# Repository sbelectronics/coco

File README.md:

# CoCo Projects

Assorted hardware and software projects for the TRS-80 Color Computer,
by Dr. Scott M. Baker — <https://www.smbaker.com/>

## [coco-bubble](coco-bubble/)

A cartridge that puts 128 KB of Intel 7110 **magnetic bubble memory**
behind a Disk BASIC-compatible command set: `DIR`, `SAVE`, `LOAD`,
`OPEN`, `COPY`, direct-access files and the rest work as they do on a
disk system, over a non-volatile solid-state medium with no moving
parts. The 16 KB ROM writes files byte-for-byte as Disk BASIC would, so
they move to and from real floppies with `COPY`, and a floppy controller
alongside it in a Multi-Pak becomes drives 1 to 3. Includes the ROM
source, the PLD for the bus interface, a parts list and assembly notes,
an emulator test suite, and a detailed account of both the hardware and
the ROM in [HOW-IT-WORKS.md](coco-bubble/HOW-IT-WORKS.md).

## [radio](radio/)

An **AM/FM radio cartridge**. Plug it in and the CoCo boots into a radio
player: big frequency digits, seek, stereo and signal indicators, twelve
named presets that live in the cartridge's own EEPROM, and audio through
the computer's TV or monitor sound. The receiver is an NXP TEF6686
car-radio tuner module; the 6809 drives it over I2C bit-banged through a
latch, and apart from the module the cartridge is just an EEPROM, a 22V10
PLD, a latch, a buffer and a dual op-amp. Works on a CoCo 1, 2 or 3,
directly or in a Multi-Pak. Includes the ROM source, the PLD, the build
tooling (the tuner's NXP firmware patch is fetched at build time, not
distributed), and [HOW-IT-WORKS.md](radio/HOW-IT-WORKS.md) on the
address decode, the tuner bring-up, how the ROM rewrites its own EEPROM,
and why seek is a host loop.

## [multicart-videocart](multicart-videocart/)

Two Raspberry Pi Pico 2 W cartridges for the CoCo 1/2 that hold your
whole ROM collection — pick a game from the OLED menu or a web browser
and the CoCo reboots straight into it. The **multicart** is the ROM
cartridge; the **videocart** is the same cartridge plus HDMI video and
audio out, rendering the VDG display by snooping the cartridge bus.
Includes firmware, schematics, gerbers, and an architectural guide in
[HOW-IT-WORKS.md](multicart-videocart/HOW-IT-WORKS.md).

## [realtalker](realtalker/)

My clone of the Colorware RealTalker speech synthesizer cartridge,
which used the Votrax SC-01-A speech IC. Includes the recreated
schematic and board files, notes on the original version 1 (CoCo 1) and
version 2 (CoCo 2) hardware, and BASIC and Python examples for driving
it.

## [cocoxt](cocoxt/)

A clone of the Burke & Burke CoCo XT hard disk interface, which puts a
PC/XT-class MFM controller (WD1002-WX1 and friends) on the CoCo's
cartridge bus, along with a long write-up on using it from **Disk
Extended Color BASIC** with B&B's Hyper-I/O rather than OS-9: setup
sequence, driver gotchas, MSA sizing, booting Hyper-I/O from ROM, and
why the address lines are inverted. Includes schematics and gerbers for
two board revisions (one adds an onboard 27C128 socket; untested) and
tools for verifying a drive image from a Gesswein MFM emulator.

## [MPI/TheLittleEngineers](MPI/TheLittleEngineers/)

A 3D-printable case (STL files) I made for the Multi-Pak Interface by
TheLittleEngineers
([CoCoDragon-MultiPakInterface](https://github.com/TheLittleEngineers/CoCoDragon-MultiPakInterface-CC-Multi-Pak_Version_1.2)).
Assembly requires M2.5 threadserts and machine screws.

## [disks](disks/)

Tools for building my disk images: a Makefile, some BASIC demo programs,
and `ccctobin.py` for converting CCC files into BIN files for the
CocoSDC.

## Related projects

- [coco-hdmi](https://github.com/sbelectronics/coco-hdmi) — an
  FPGA-based interposer (Tang Nano 9K) that adds native digital HDMI
  output to the CoCo 2 by intercepting the VDG's signals, rendering
  video at 720×480p with 48 kHz audio.

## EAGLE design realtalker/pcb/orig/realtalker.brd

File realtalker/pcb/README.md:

Colorware Realtalker Schematics
http://www.smbaker.com/

NOTE! CAUTION! These schematics are unverified.

These directories contain reverse-engineered schematics for the
colorware realtalker for the trs-80 color computer. Note that the
version 1 of the realtalker was for coco-1 only as it relied on
the +12V from the cartridge port. A version-2 was added for the coco-2
which at a minimum included an external power supply. I also found
that the version-1 when used on a Coco-2 produces audio that is
clipped and distorted. Adding a potentiometer between the realtalker's
output and the coco's cartridge sound input resolved this issue for
me. Unknown what other changes the version-2 may have included.

Also present is a schematic for a revised version that I am working
on that will include a few minor improvements.

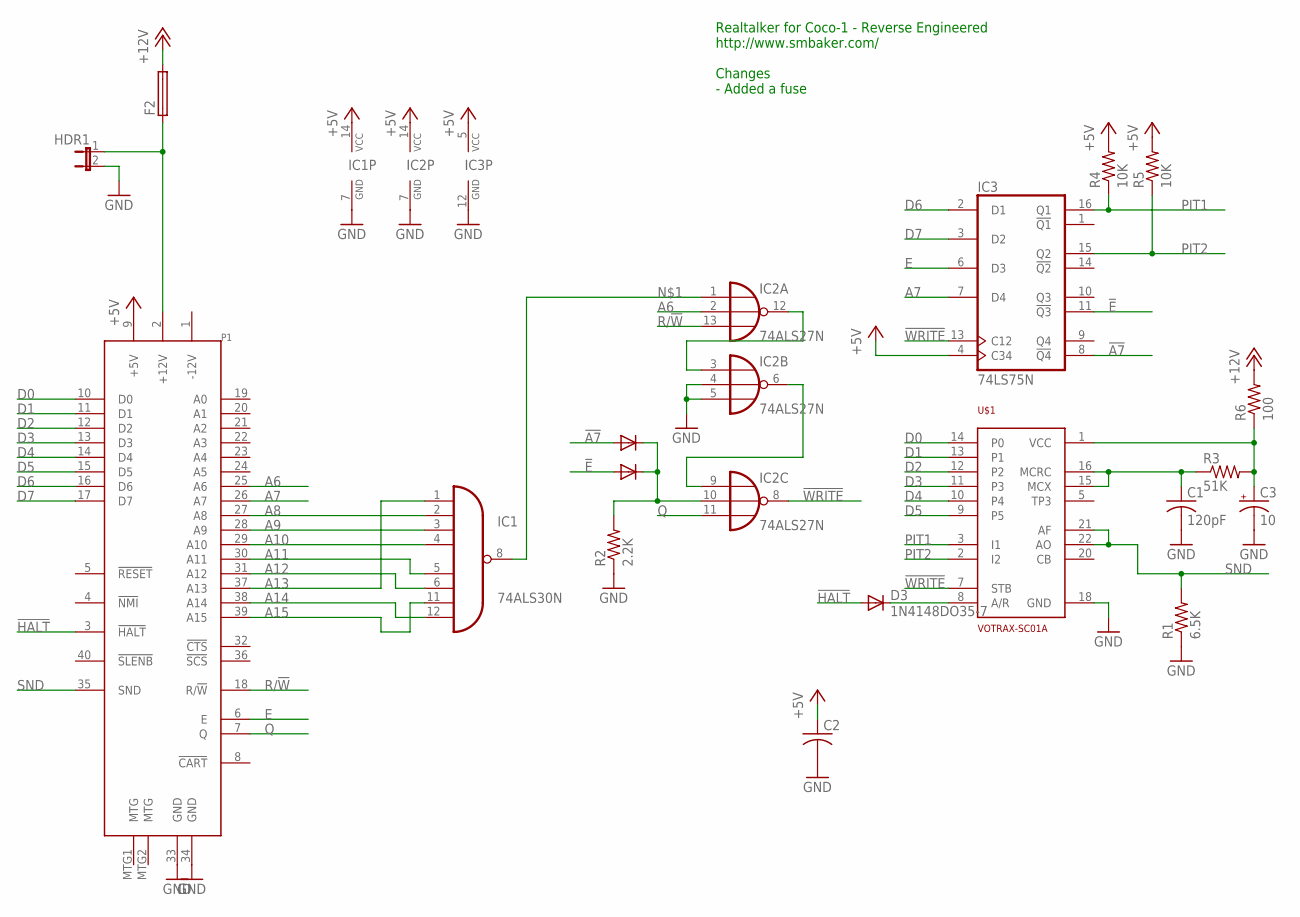
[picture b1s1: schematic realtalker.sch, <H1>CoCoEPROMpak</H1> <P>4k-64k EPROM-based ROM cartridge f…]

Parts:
C1: 120pF; C025-025X050
C2: C-US025-025X050; C025-025X050
C3: 10; E2,5-6
D1, D2, D3: 1N4148DO35-7; DO35-7
F2: PTC_FUSE; PTC_0.400
HDR1: JP1E; JP1
IC1: 74ALS30N; DIL14
IC2: 74ALS27N; DIL14
IC3: 74LS75N; DIL16
P1: COCO-CARTRT; COCO-CART-RT
R1: 6.5K; 0204/7
R2: 2.2K; 0204/7
R3: 51K; 0204/7
R4, R5: 10K; 0204/7
R6: 100; 0204/7
U$1: VOTRAX-SC01A; DIL22-4

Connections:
!A7: D2.A, IC3.8 (!Q4)
!E: D1.A, IC3.11 (!Q3)
!HALT: D3.A, P1.3 (!HALT)
!WRITE: IC2.8 (O), IC3.13 (C12), U$1.7 (STB)
+5V: C2.1, IC1.14 (VCC), IC2.14 (VCC), IC3.4 (C34), IC3.5 (VCC), P1.9 (+5V), R4.2, R5.2
+12V: F2.2, R6.2
A6: IC2.2 (I1), P1.25 (A6)
A7: IC3.7 (D4), P1.26 (A7)
A8: IC1.2 (I1), P1.27 (A8)
A9: IC1.3 (I2), P1.28 (A9)
A10: IC1.4 (I3), P1.29 (A10)
A11: IC1.5 (I4), P1.30 (A11)
A12: IC1.6 (I5), P1.31 (A12)
A13: IC1.1 (I0), P1.37 (A13)
A14: IC1.12 (I7), P1.38 (A14)
A15: IC1.11 (I6), P1.39 (A15)
D0: P1.10 (D0), U$1.14 (P0)
D1: P1.11 (D1), U$1.13 (P1)
D2: P1.12 (D2), U$1.12 (P2)
D3: P1.13 (D3), U$1.11 (P3)
D4: P1.14 (D4), U$1.10 (P4)
D5: P1.15 (D5), U$1.9 (P5)
D6: IC3.2 (D1), P1.16 (D6)
D7: IC3.3 (D2), P1.17 (D7)
E: IC3.6 (D3), P1.6 (E)
GND: C1.2, C2.2, C3.-, HDR1.2, IC1.7 (GND), IC2.4 (I1), IC2.5 (I2), IC2.7 (GND), IC3.12 (GND), P1.33 (GND), P1.34 (GND), R1.1, R2.1, U$1.18 (GND)
unnamed: IC1.8 (O), IC2.1 (I0)
unnamed: D3.C, U$1.8 (A/R)
unnamed: C1.1, R3.1, U$1.15 (MCX), U$1.16 (MCRC)
unnamed: F2.1, HDR1.1, P1.2 (+12V)
unnamed: C3.+, R3.2, R6.1, U$1.1 (VCC)
unnamed: IC2.3 (I0), IC2.12 (O)
unnamed: IC2.6 (O), IC2.9 (I0)
unnamed: D1.C, D2.C, IC2.10 (I1), R2.2
PIT1: IC3.16 (Q1), R4.1, U$1.3 (I1)
PIT2: IC3.15 (Q2), R5.1, U$1.2 (I2)
Q: IC2.11 (I2), P1.7 (Q)
R/!W: IC2.13 (I2), P1.18 (R/!W)
SND: P1.35 (SND), R1.2, U$1.21 (AF), U$1.22 (AO)

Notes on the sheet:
Realtalker for Coco-1 - Reverse Engineered http://www.smbaker.com/ Changes - Added a fuse

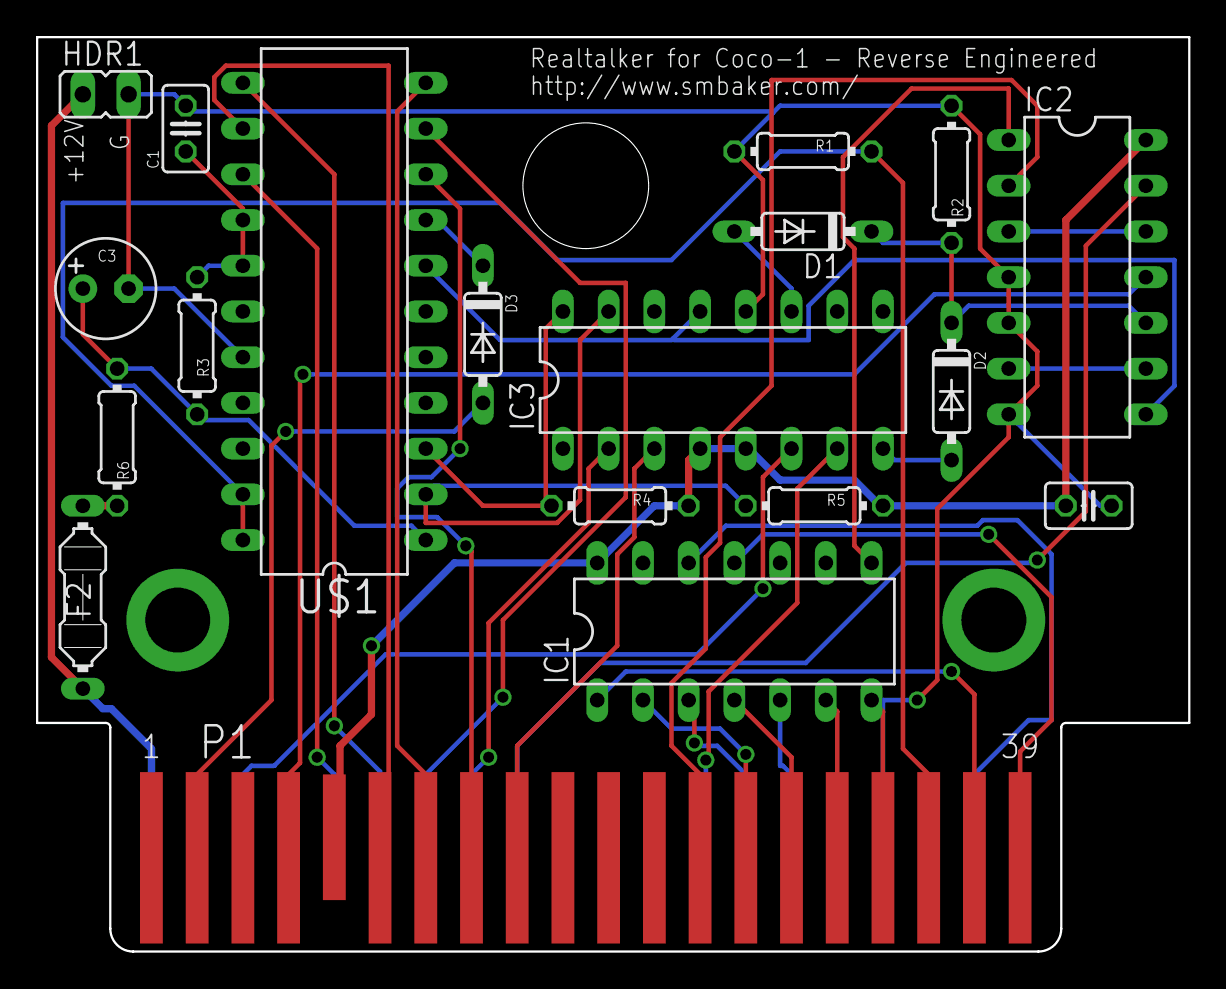
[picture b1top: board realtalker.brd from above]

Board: 2 copper layers, 64.0 x 50.8 mm, 19 parts (0 on the bottom side), 39 nets.

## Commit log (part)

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2021-09-19 ccctobin.py, convert CCC cartridge roms to BIN
2021-09-27 Add 3D Printed Case for TheLittleEngineers MPI
2021-10-02 speech/sound sample basic programs, with bugs fixed
2021-10-02 basic disk makefile
2021-10-04 realtalker stuff
2021-10-04 more readme stuff

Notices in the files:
realtalker/pcb/orig/realtalker.brd:
Copyright 2013 Mark J. Blair
Distributed under GPLv3
CoCoEPROMpak is a free hardware design: you can redistribute it and/or modify it under the terms of the GNU General Public License as published by the Free Software Foundation, either version 3 of the License, or (at your option) any later version.
